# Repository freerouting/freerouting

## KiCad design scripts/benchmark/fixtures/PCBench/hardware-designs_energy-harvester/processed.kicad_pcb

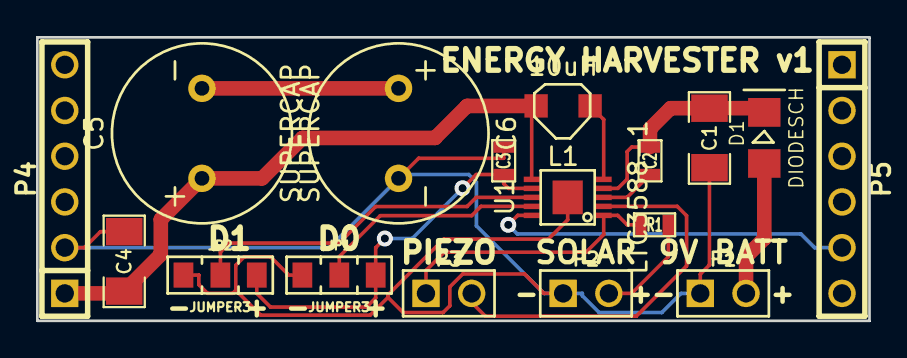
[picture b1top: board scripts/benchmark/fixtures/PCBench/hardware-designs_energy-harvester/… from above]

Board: 2 copper layers, 46.2 x 15.7 mm, 18 parts (1 on the bottom side), 14 nets.

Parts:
C1: 100uF; SM1206
C2: 1uF; SM0603
C3: 4.7uF; SM0603
C4: 10uF; SM1206
C5, C6: SUPERCAP; SUPERCAP_ESHSR-0010C0-002R7
D1: DIODESCH; DIODE-1206
JP1, JP2: JUMPER3; SM0805_JUMPER3
L1: 10uH; INDUCTOR-CDRH2D18-LD
Noname_1: LOGO_SNOWCAP_BACK
P1, P2, P3: CONN_2; PIN_ARRAY_2X1
P4, P5: CONN_6; PIN_ARRAY-6X1
R1: 300R; SM0603
U1: LTC3588-1; LTC3588-1-MSOP10

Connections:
/PGOOD: P5.5, U1.10
/VIN2: C3.1, JP1.3, JP2.3, U1.7
GND: C1.2, C3.2, C4.2, C6.2, JP1.1, JP2.1, P1.1, P2.1, P4.2, U1.11
unnamed: P3.1, R1.2, U1.1
unnamed: P3.2, U1.2
unnamed: JP2.2, U1.8
unnamed: C5.2, C6.1
unnamed: JP1.2, U1.9
unnamed: D1.1, P1.2
unnamed: C2.2, U1.3
unnamed: P2.2, R1.1
unnamed: L1.1, U1.5
unnamed: C1.1, C2.1, D1.2, U1.4
VCC: C4.1, C5.1, L1.2, P4.1, U1.6

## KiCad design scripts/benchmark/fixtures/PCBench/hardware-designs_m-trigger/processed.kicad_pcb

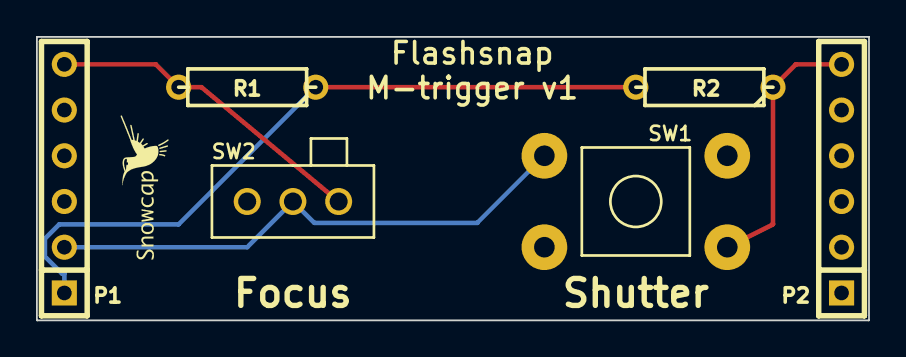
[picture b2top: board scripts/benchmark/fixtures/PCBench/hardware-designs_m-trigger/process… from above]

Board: 2 copper layers, 46.2 x 15.7 mm, 7 parts (0 on the bottom side), 4 nets.

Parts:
P1, P2: CONN_6; SIL-6
R1, R2: R; R3
SW1: SW_PUSH; SW_PUSH_6MM
SW2: DUAL_SWITCH_INV; SLIDE_SWITCH
VAL: REF; LOGO_SNOWCAP_FRONT_SMALL

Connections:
unnamed: P1.6, R1.2, SW2.1
unnamed: P2.6, R2.1, SW1.2
unnamed: P1.2, SW1.1, SW2.2
unnamed: P1.1, R1.1, R2.2

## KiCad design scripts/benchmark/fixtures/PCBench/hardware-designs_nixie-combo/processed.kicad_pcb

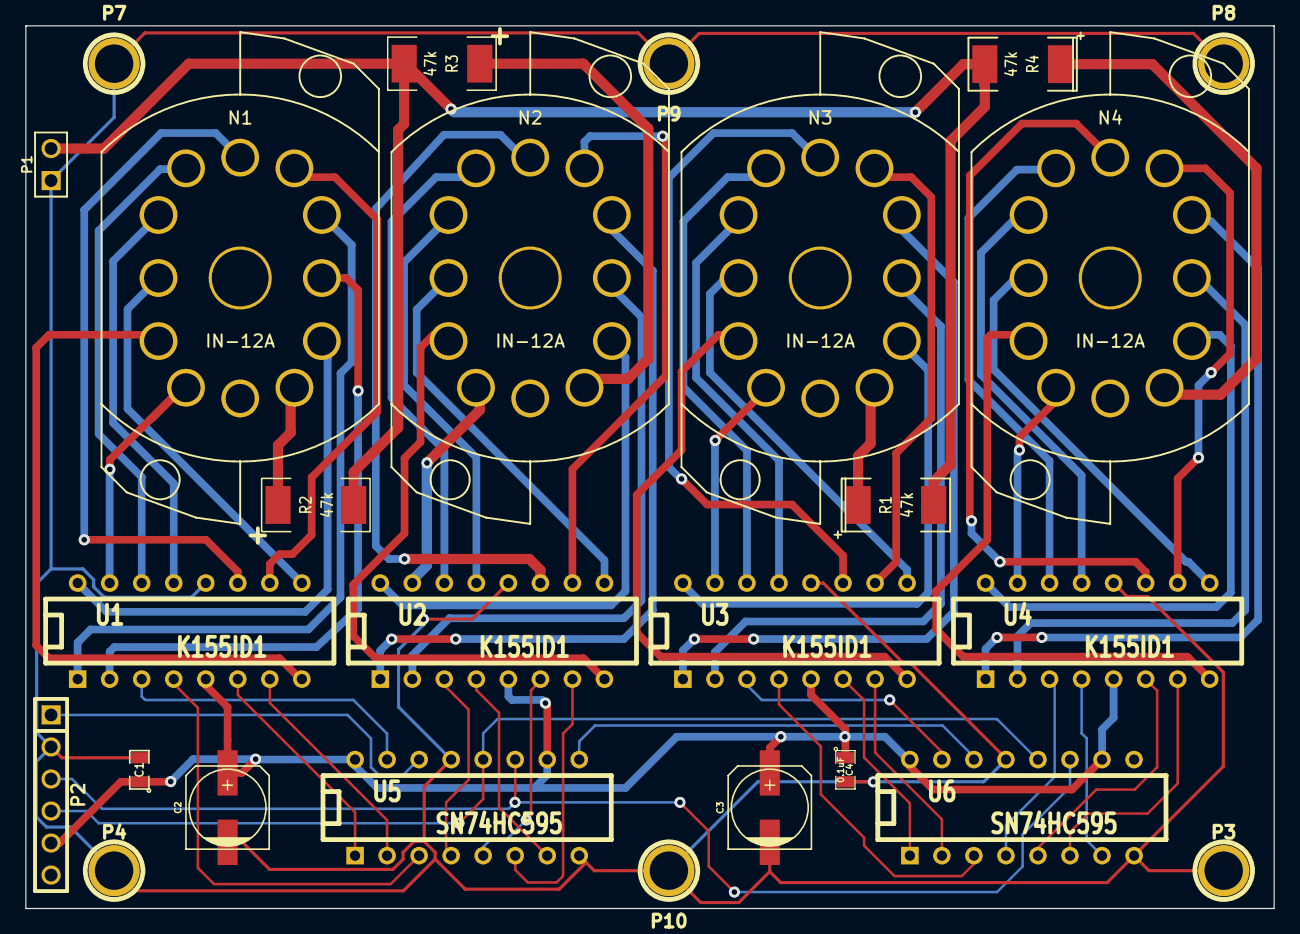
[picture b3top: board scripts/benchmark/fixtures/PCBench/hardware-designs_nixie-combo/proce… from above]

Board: 2 copper layers, 99.0 x 70.0 mm, 27 parts (1 on the bottom side), 67 nets.

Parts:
C1, C4: 0.1uF; SM0805
C2, C3: 100uF; c_elec_6.3x7.7
N1, N2, N3, N4: IN-12A; IN-12A-SOCKET
Noname_1: LOGO_SNOWCAP_BACK
P1: CONN_2; PIN_ARRAY_2X1
P2: CONN_6; PIN_ARRAY-6X1
P3, P4, P7, P8, P9, P10: CONN_1; 1pin
R1, R2, R3, R4: 47k; SM2512
U1, U2, U3, U4: K155ID1; DIP-16__300
U5, U6: SN74HC595; DIP-16__300

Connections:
+3.3V: C1.1, C2.1, C3.1, C4.1, P2.5, U1.5, U2.5, U3.5, U4.5, U5.10, U5.16, U6.10, U6.16
/a0: N1.2, U1.16
/a1: N1.11, U1.15
/a2: N1.10, U1.8
/a3: N1.9, U1.9
/a4: N1.8, U1.13
/a5: N1.7, U1.14
/a6: N1.6, U1.11
/a7: N1.5, U1.10
/a8: N1.4, U1.1
/a9: N1.3, U1.2
/b0: N2.2, U2.16
/b1: N2.11, U2.15
/b2: N2.10, U2.8
/b3: N2.9, U2.9
/b4: N2.8, U2.13
/b5: N2.7, U2.14
/b6: N2.6, U2.11
/b7: N2.5, U2.10
/b8: N2.4, U2.1
/b9: N2.3, U2.2
/c0: N3.2, U3.16
/c1: N3.11, U3.15
/c2: N3.10, U3.8
/c3: N3.9, U3.9
/c4: N3.8, U3.13
/c5: N3.7, U3.14
/c6: N3.6, U3.11
/c7: N3.5, U3.10
/c8: N3.4, U3.1
/c9: N3.3, U3.2
/d0: N4.2, U4.16
/d1: N4.11, U4.15
/d2: N4.10, U4.8
/d3: N4.9, U4.9
/d4: N4.8, U4.13
/d5: N4.7, U4.14
/d6: N4.6, U4.11
/d7: N4.5, U4.10
/d8: N4.4, U4.1
/d9: N4.3, U4.2
GND: C1.2, C2.2, C3.2, C4.2, P1.1, P2.2, P3.1, P4.1, P7.1, P8.1, P9.1, P10.1, U1.12, U2.12, U3.12, U4.12, U5.8, U5.13, U6.8, U6.13
HT: P1.2, R1.2, R2.2, R3.2, R4.2
unnamed: N4.1, R4.1
unnamed: U4.7, U6.6
unnamed: U4.4, U6.7
unnamed: U4.3, U6.4
unnamed: U3.7, U6.2
unnamed: U3.6, U6.1
unnamed: U3.4, U6.3
unnamed: N1.1, R2.1
unnamed: N2.1, R3.1
unnamed: N3.1, R1.1
unnamed: U3.3, U6.15
unnamed: U4.6, U6.5
unnamed: U5.9, U6.14
unnamed: P2.4, U5.12, U6.12
unnamed: P2.3, U5.11, U6.11
unnamed: P2.1, U5.14
unnamed: U2.4, U5.7
unnamed: U2.7, U5.6
unnamed: U2.6, U5.5
unnamed: U2.3, U5.4
unnamed: U1.4, U5.3
unnamed: U1.7, U5.2
unnamed: U1.6, U5.1
unnamed: U1.3, U5.15
